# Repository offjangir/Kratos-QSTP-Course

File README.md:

# Kratos-QSTP
* Course was offered by [Kratos-Mars Rover Mission Team,Bits Pilani](https://kratosbitsgoa.com)
* Course Repository : [QSTP-Kratos_electronics](https://github.com/adbidwai/QSTP-Kratos_electronics)

### Learned Basics of During the Course Work 
* Arduino 
* Python 
* Robotic Operating System (ROS)
* PCB Designing  
* Control Theory and  PID Controllers

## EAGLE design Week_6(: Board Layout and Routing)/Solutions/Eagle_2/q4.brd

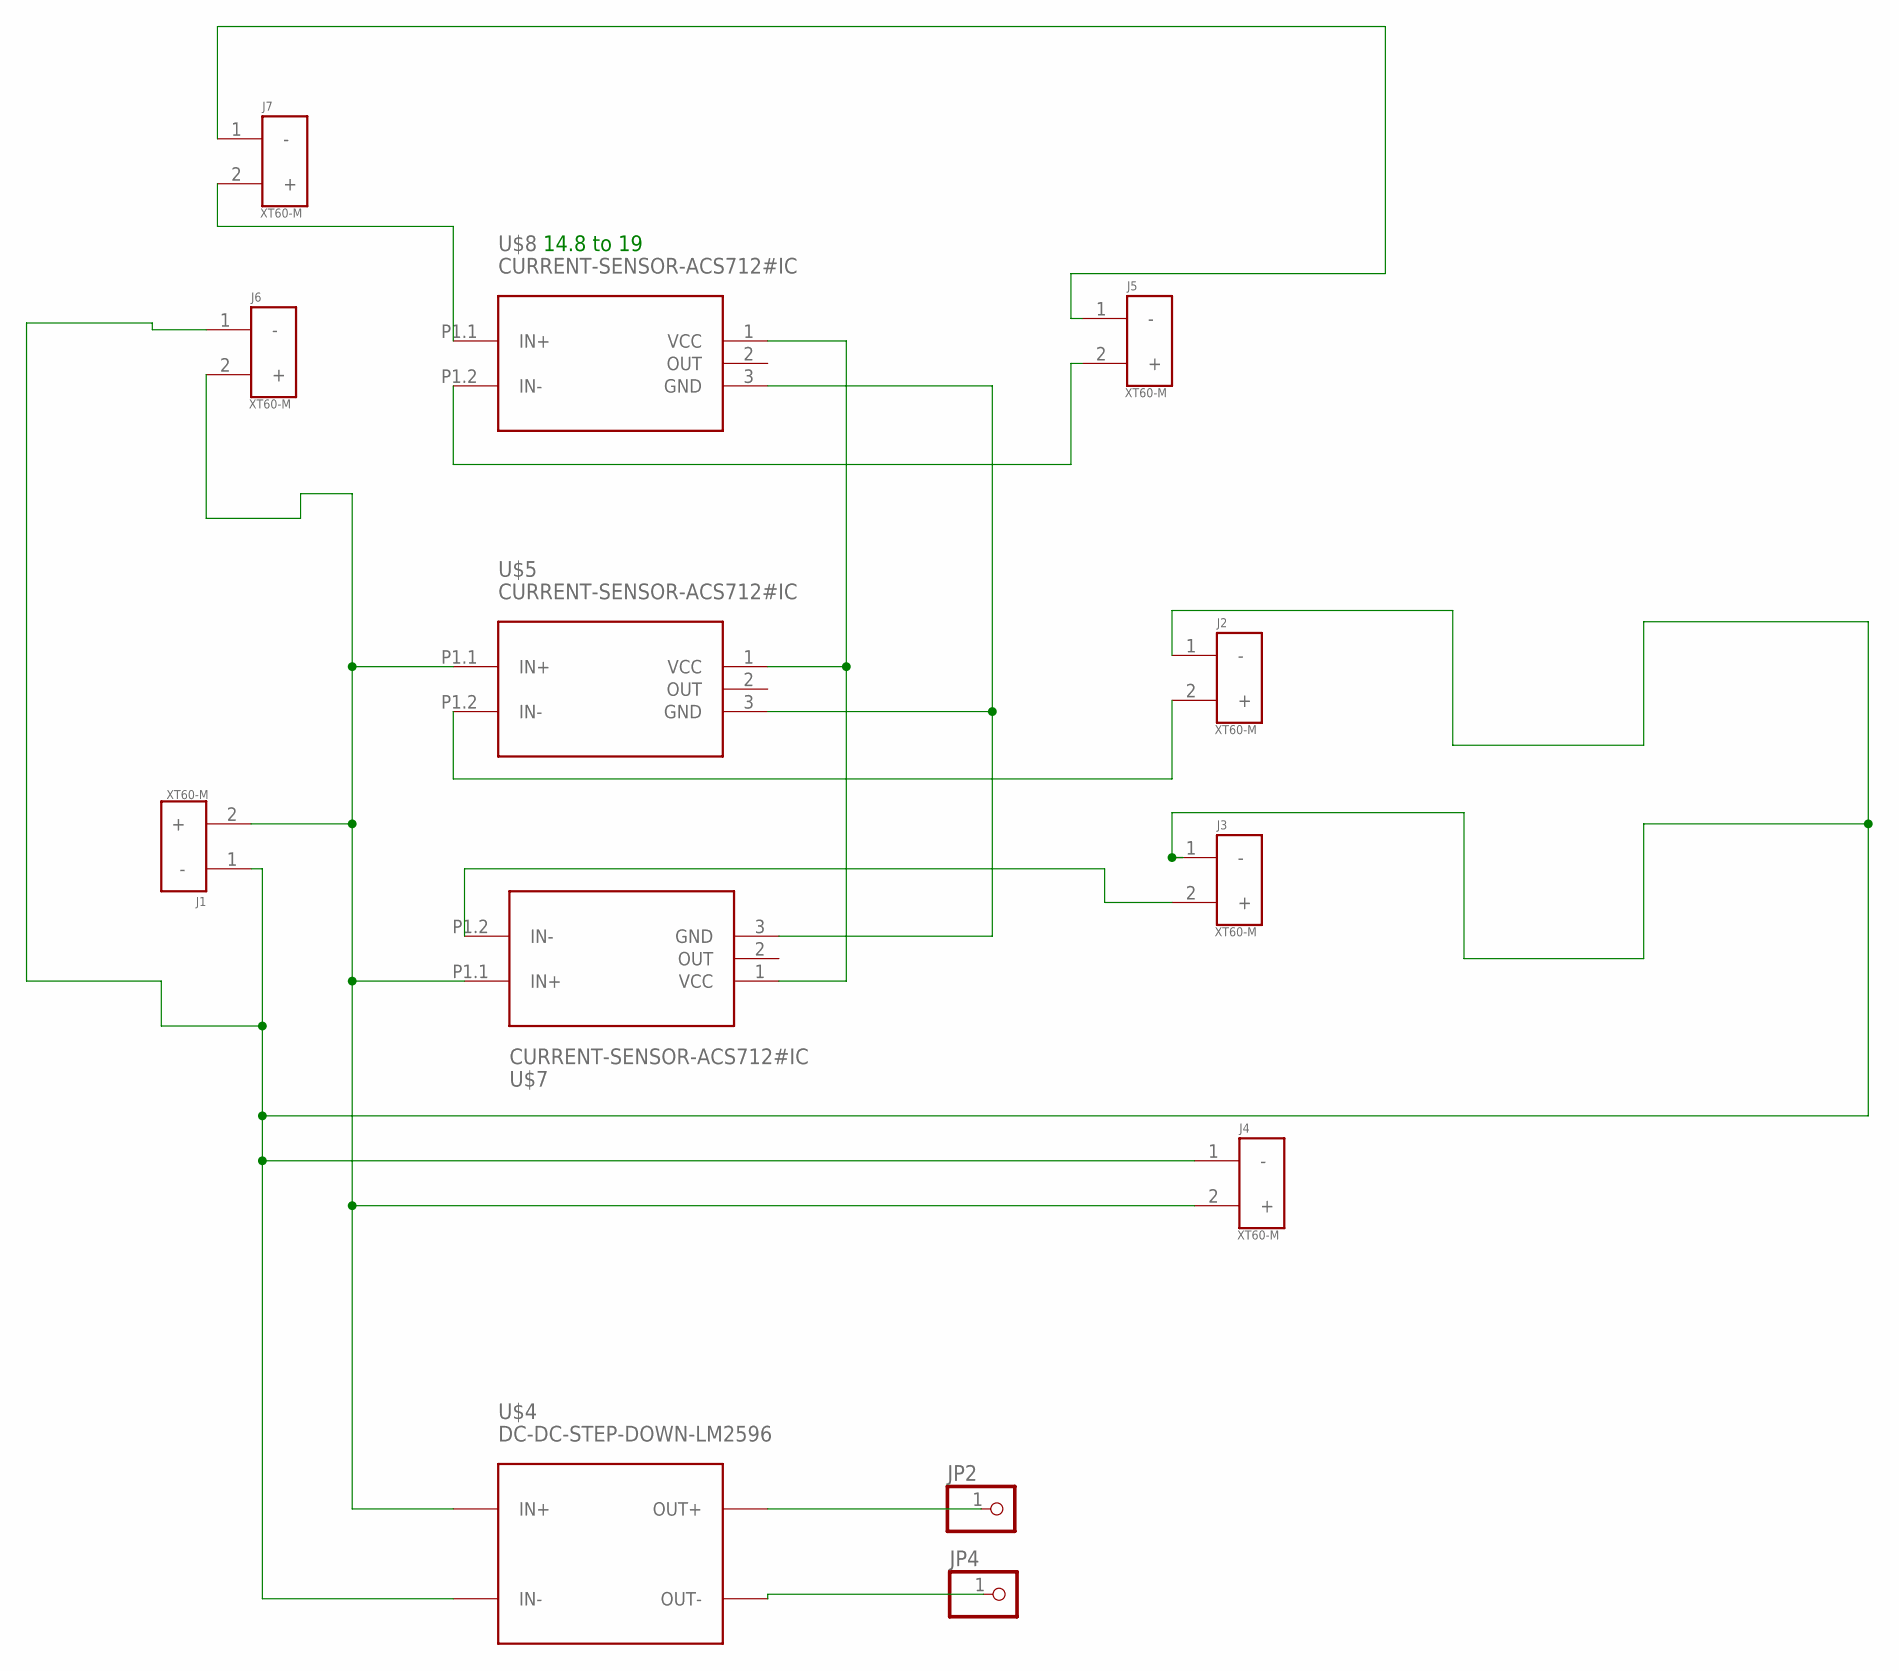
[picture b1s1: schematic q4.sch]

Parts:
J1, J2, J3, J4, J5, J6, J7: XT60-M; AMASS_XT60-M
JP2, JP4: PINHD-1X1; 1X01
U$4: DC-DC-STEP-DOWN-LM2596
U$5, U$7, U$8: CURRENT-SENSOR-ACS712#IC

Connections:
unnamed: J7.2 (+), U$8.P1.1 (IN+)
unnamed: J1.1 (-), J2.1 (-), J3.1 (-), J4.1 (-), J6.1 (-), U$4.IN-
unnamed: J5.1 (-), J7.1 (-)
unnamed: J1.2 (+), J4.2 (+), J6.2 (+), U$4.IN+, U$5.P1.1 (IN+), U$7.P1.1 (IN+)
unnamed: J2.2 (+), U$5.P1.2 (IN-)
unnamed: JP4.1, U$4.OUT-
unnamed: J3.2 (+), U$7.P1.2 (IN-)
unnamed: J5.2 (+), U$8.P1.2 (IN-)
unnamed: JP2.1, U$4.OUT+
unnamed: U$5.1 (VCC), U$7.1 (VCC), U$8.1 (VCC)
unnamed: U$5.3 (GND), U$7.3 (GND), U$8.3 (GND)

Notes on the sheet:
14.8 to 19

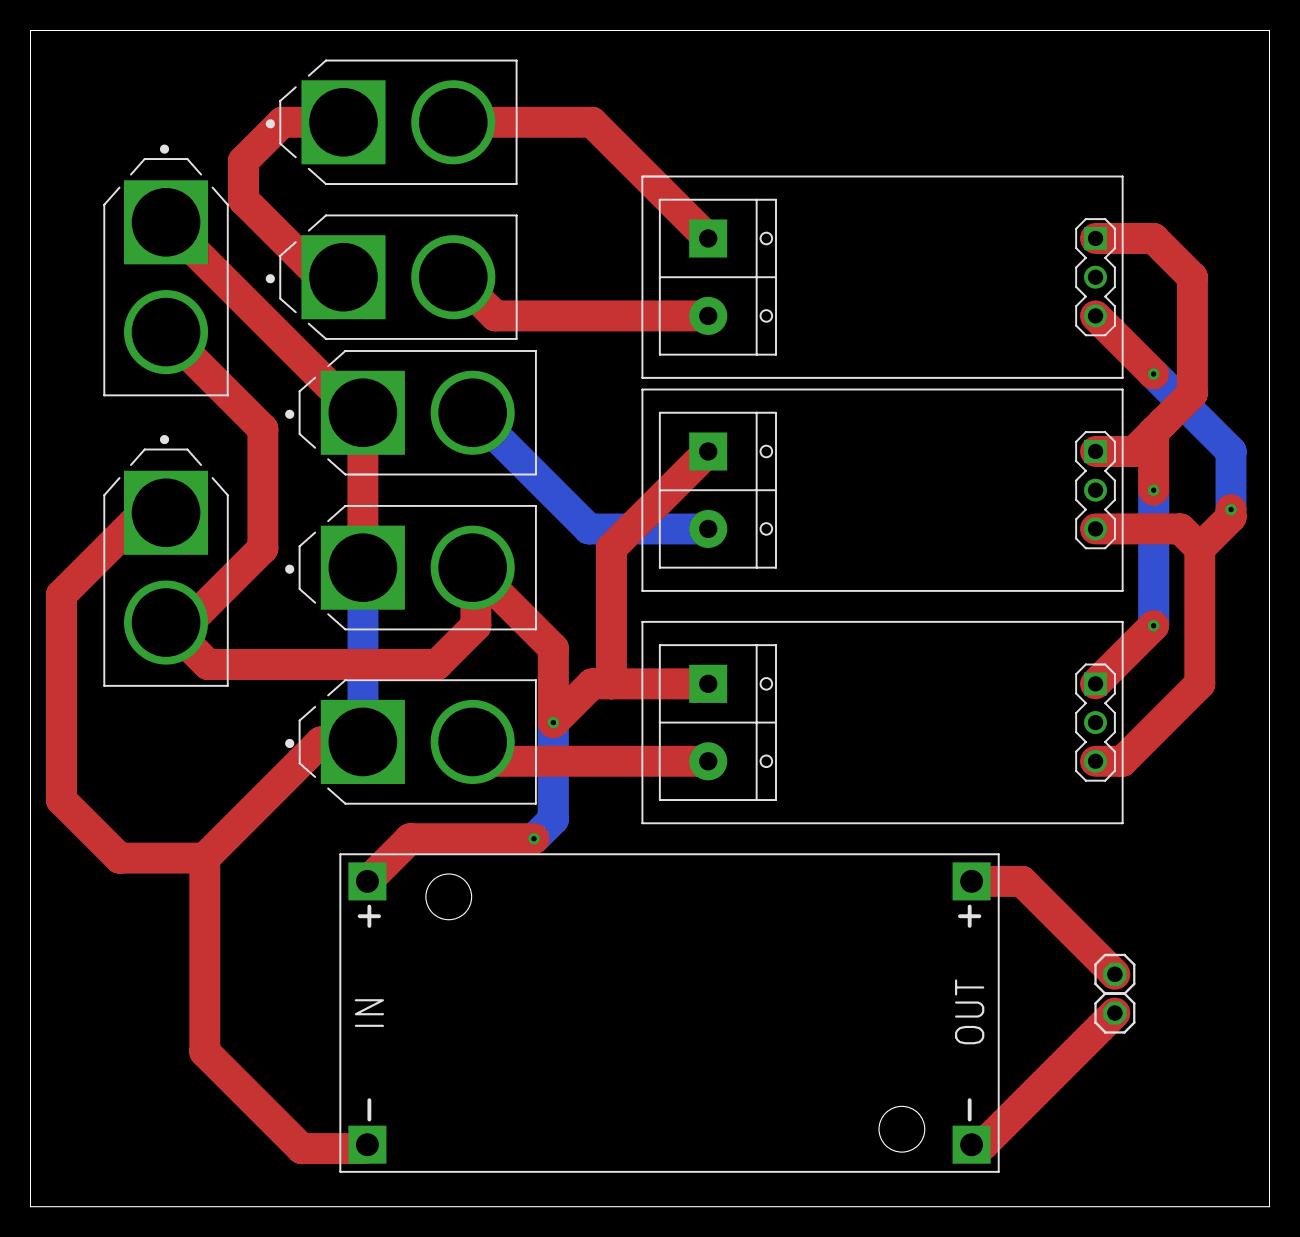
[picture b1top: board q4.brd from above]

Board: 2 copper layers, 81.3 x 77.1 mm, 13 parts (0 on the bottom side), 11 nets.

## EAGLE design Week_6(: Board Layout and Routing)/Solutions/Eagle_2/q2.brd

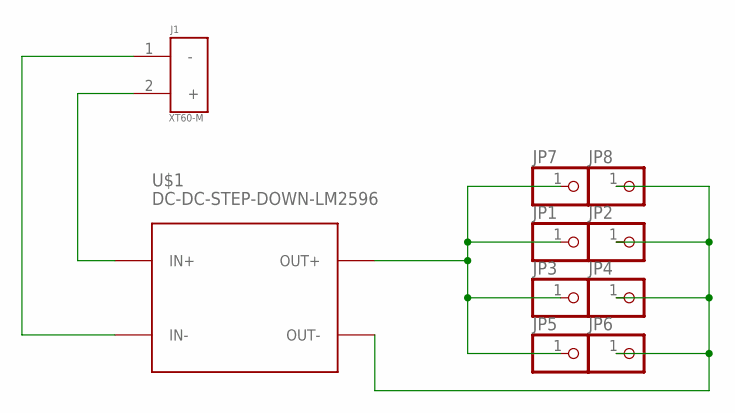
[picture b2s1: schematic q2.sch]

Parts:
J1: XT60-M; AMASS_XT60-M
JP1, JP2, JP3, JP4, JP5, JP6, JP7, JP8: PINHD-1X1; 1X01
U$1: DC-DC-STEP-DOWN-LM2596

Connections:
unnamed: J1.2 (+), U$1.IN+
unnamed: J1.1 (-), U$1.IN-
unnamed: JP1.1, JP3.1, JP5.1, JP7.1, U$1.OUT+
unnamed: JP2.1, JP4.1, JP6.1, JP8.1, U$1.OUT-

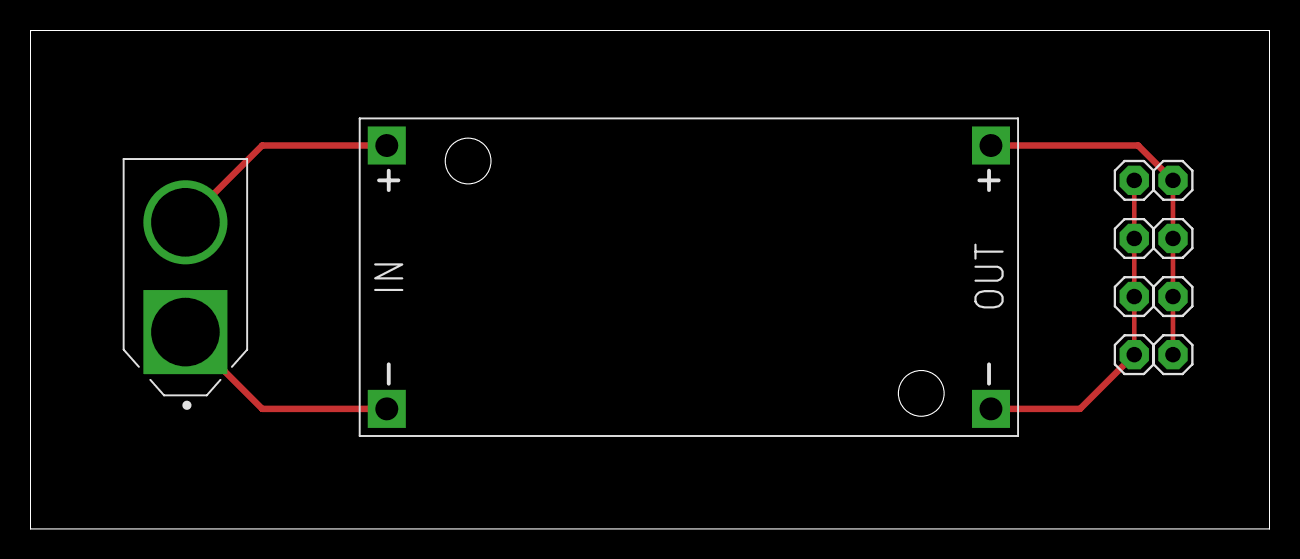
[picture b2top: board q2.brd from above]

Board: 2 copper layers, 81.3 x 32.7 mm, 10 parts (0 on the bottom side), 4 nets.

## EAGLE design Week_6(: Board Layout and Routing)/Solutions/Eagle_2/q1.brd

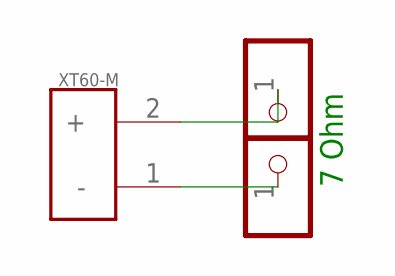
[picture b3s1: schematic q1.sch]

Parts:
J1: XT60-M; AMASS_XT60-M
JP1, JP2: PINHD-1X1; 1X01

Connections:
unnamed: J1.2 (+), JP1.1
unnamed: J1.1 (-), JP2.1

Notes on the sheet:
7 Ohm

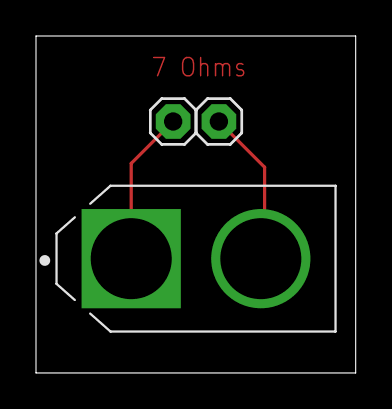
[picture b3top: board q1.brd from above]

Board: 2 copper layers, 17.8 x 18.7 mm, 3 parts (0 on the bottom side), 2 nets.

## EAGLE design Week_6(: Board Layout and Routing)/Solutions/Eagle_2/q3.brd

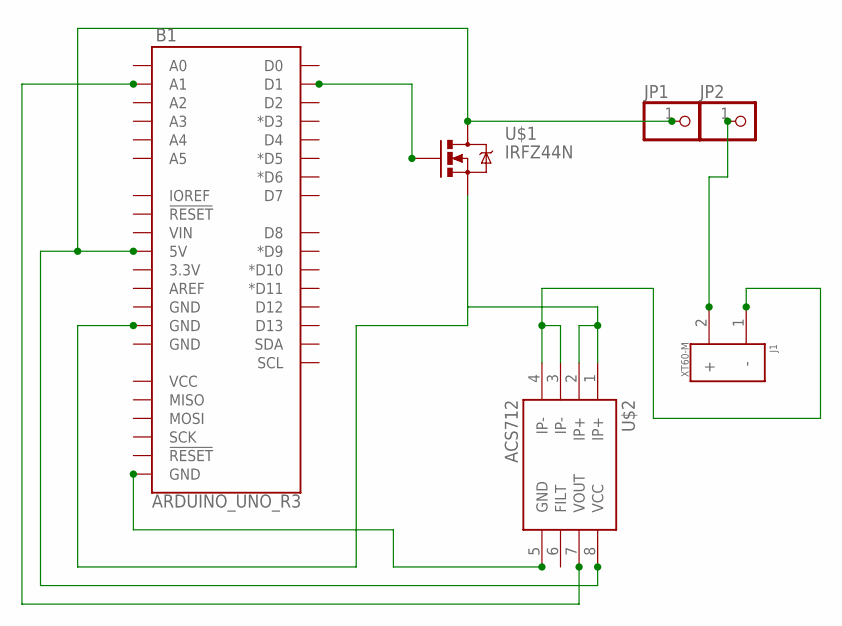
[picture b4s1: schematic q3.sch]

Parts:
B1: ARDUINO_UNO_R3; ARDUINO_R3
J1: XT60-M; AMASS_XT60-M
JP1, JP2: PINHD-1X1; 1X01
U$1: IRFZ44N; TO-220
U$2: ACS712; SO08

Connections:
unnamed: J1.1 (-), U$2.3 (IP-), U$2.4 (IP-)
unnamed: J1.2 (+), JP2.1
unnamed: B1.5V, JP1.1, U$1.2 (D), U$2.8 (VCC)
unnamed: B1.GND@3 (GND), U$1.3 (S), U$2.1 (IP+), U$2.2 (IP+)
unnamed: B1.D1, U$1.1 (G)
unnamed: B1.A1, U$2.7 (VOUT)
unnamed: B1.GND@1 (GND), U$2.5 (GND)

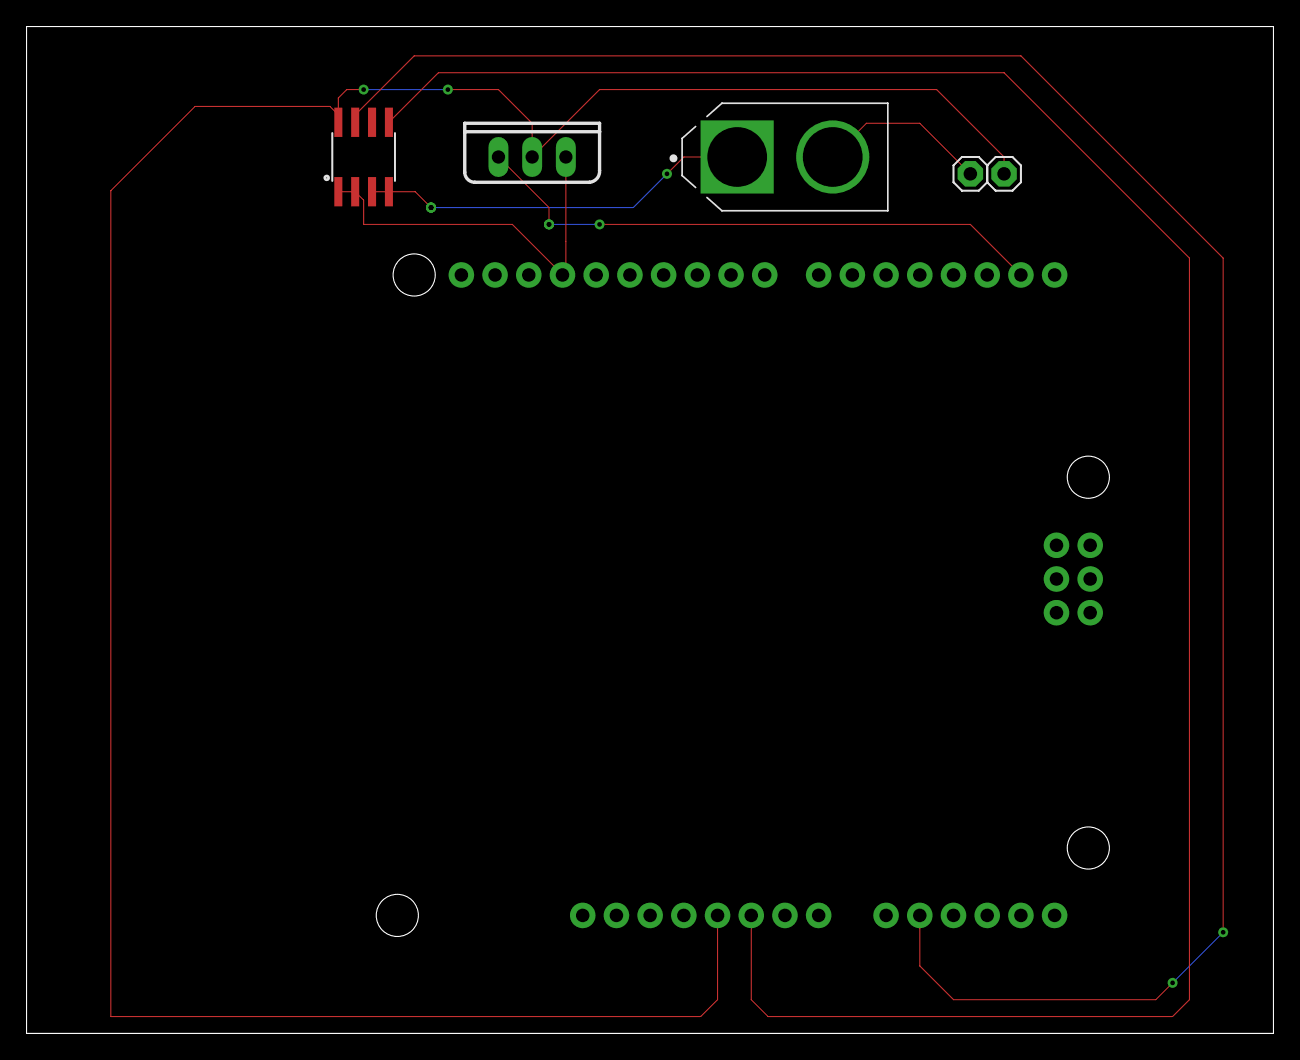
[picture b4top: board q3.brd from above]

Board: 2 copper layers, 94.0 x 75.9 mm, 6 parts (0 on the bottom side), 7 nets.

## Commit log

2020-08-03 some basic intro of week 1-2
2020-08-03 week 3 brief
2020-08-03 final readme
2020-08-03 Final Repo

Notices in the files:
parts and their libraries:
diy-modules: Released under the Creative Commons Attribution 4.0 International License: http://creativecommons.org/licenses/by/4.0
SparkFun-Boards: Licensing: Creative Commons ShareAlike 4.0 International - https://creativecommons.org/licenses/by-sa/4.0
